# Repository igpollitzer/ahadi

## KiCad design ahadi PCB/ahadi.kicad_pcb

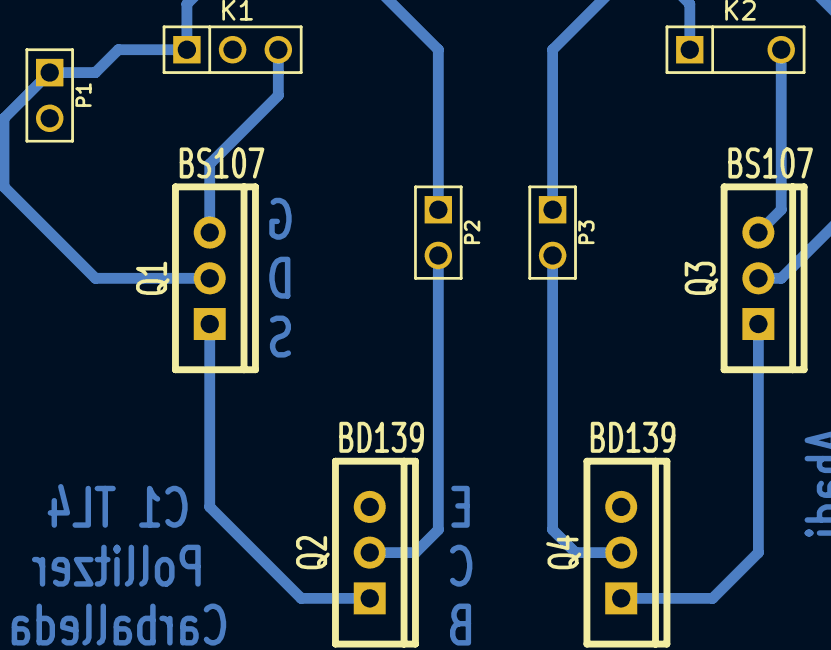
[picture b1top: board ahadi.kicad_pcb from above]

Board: 2 copper layers, 9 parts (0 on the bottom side), 9 nets.

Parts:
K1, K2: CONN_3; PIN_ARRAY_3X1
P1, P2, P3: CONN_2; PIN_ARRAY_2X1
Q1, Q3: BS107; TO220_VERT
Q2, Q4: BD139; TO220_VERT

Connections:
unnamed: P3.2, Q4.2
unnamed: K2.3, Q3.2
unnamed: K2.2, Q4.1
unnamed: Q3.3, Q4.3
unnamed: K1.1, K2.1, P1.1, P2.1, P3.1, Q1.1, Q3.1
unnamed: K1.2, P1.2, Q2.1
unnamed: P2.2, Q2.2
unnamed: K1.3, Q1.2
unnamed: Q1.3, Q2.3

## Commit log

2016-11-23 TP terminado.
